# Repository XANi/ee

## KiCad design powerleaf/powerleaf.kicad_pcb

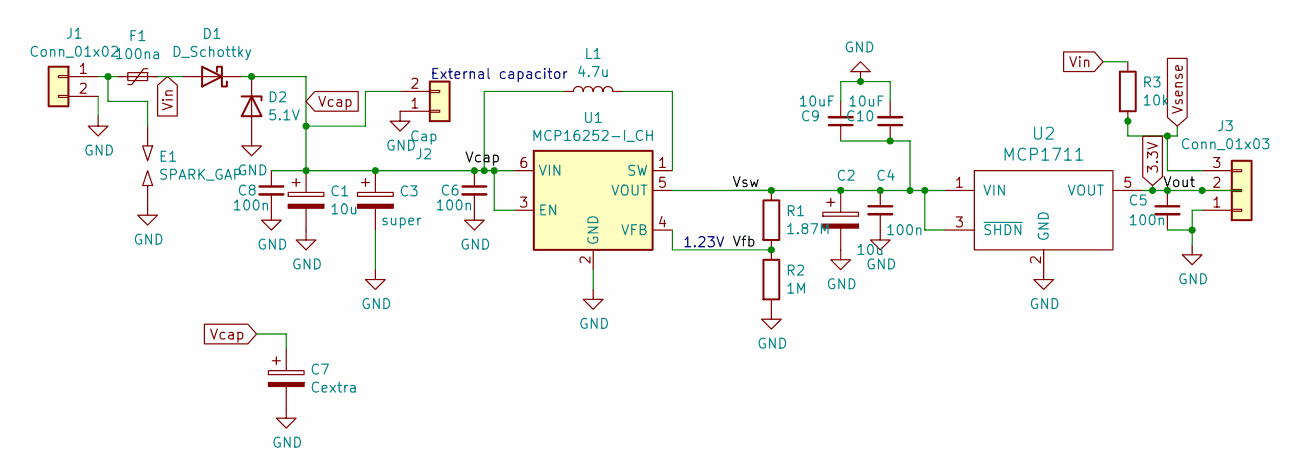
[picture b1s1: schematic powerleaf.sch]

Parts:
C1, C2: 10u; C_0805_2012Metric_Pad1.15x1.40mm_HandSolder
C3: super; CP_Radial_D10.0mm_P2.50mm_P5.00mm
C4, C5, C6: 100n; C_0805_2012Metric_Pad1.15x1.40mm_HandSolder
C7: Cextra; CP_Elec_6.3x7.7
C8: 100n; C_0805_2012Metric_Pad1.18x1.45mm_HandSolder
C9, C10: 10uF; C_0805_2012Metric_Pad1.18x1.45mm_HandSolder
D1: D_Schottky; D_0805_2012Metric_Pad1.15x1.40mm_HandSolder
D2: 5.1V; D_0805_2012Metric_Pad1.15x1.40mm_HandSolder
E1: SPARK_GAP; SparkGap-0.3mm
F1: 100na; R_Axial_DIN0204_L3.6mm_D1.6mm_P5.08mm_Vertical
J1: Conn_01x02; PinHeader_1x02_P2.54mm_Vertical
J2: Cap; PinHeader_1x02_P2.54mm_Vertical
J3: Conn_01x03; PinHeader_1x03_P2.54mm_Vertical
L1: 4.7u; L_Vishay_IHLP-1616
R1: 1.87M; R_0805_2012Metric_Pad1.15x1.40mm_HandSolder
R2: 1M; R_0805_2012Metric_Pad1.15x1.40mm_HandSolder
R3: 10k; R_0805_2012Metric_Pad1.15x1.40mm_HandSolder
U1: MCP16252-I_CH; SOT-23-6_Handsoldering
U2: MCP1711; SOT-23-6_Handsoldering

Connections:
3.3V: C5.1, J3.2, U2.5 (VOUT)
/Vfb: R1.2, R2.1, U1.4 (VFB)
/Vsw: C2.1, C4.1, C9.1, C10.1, R1.1, U1.5 (VOUT), U2.1 (VIN), U2.3 (~SHDN)
GND: C1.2, C2.2, C3.2, C4.2, C5.2, C6.2, C7.2, C8.2, C9.2, C10.2, D2.2 (A), E1.2, J1.2, J2.1, J3.1, R2.2, U1.2 (GND), U2.2 (GND)
unnamed: E1.1, F1.2, J1.1
unnamed: L1.2, U1.1 (SW)
Vcap: C1.1, C3.1, C6.1, C7.1, C8.1, D1.1 (K), D2.1 (K), J2.2, L1.1, U1.3 (EN), U1.6 (VIN)
Vin: D1.2 (A), F1.1, R3.1
Vsense: J3.3, R3.2

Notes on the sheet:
1.23V
External capacitor

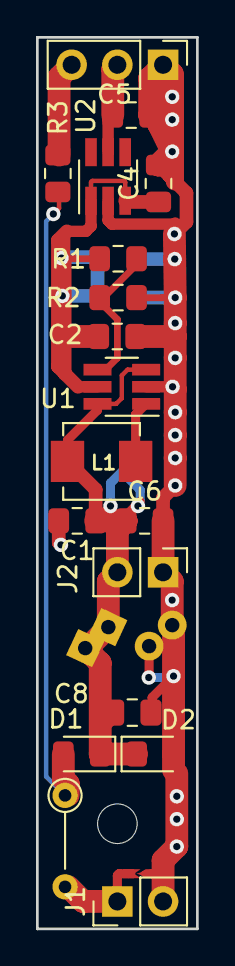
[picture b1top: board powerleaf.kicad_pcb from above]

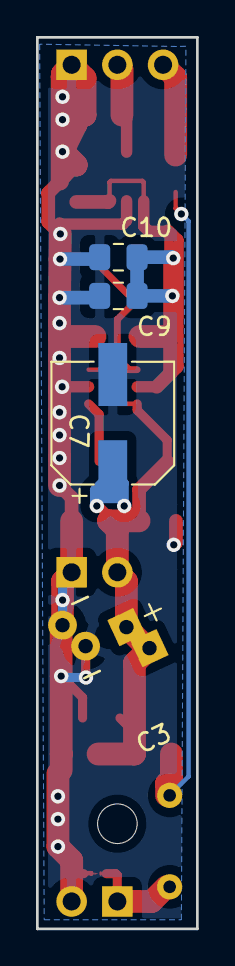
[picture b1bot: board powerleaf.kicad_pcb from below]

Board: 2 copper layers, 8.9 x 49.5 mm, 23 parts (4 on the bottom side), 9 nets.

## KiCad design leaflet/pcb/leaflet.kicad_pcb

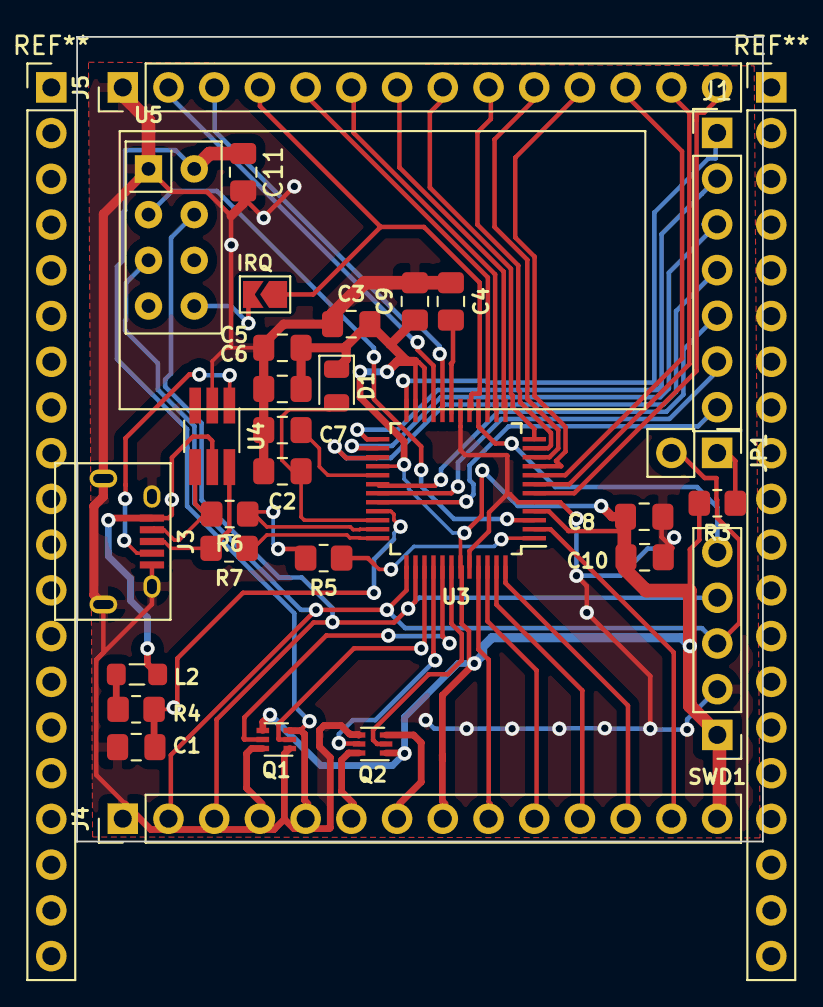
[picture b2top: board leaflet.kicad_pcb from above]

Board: 2 copper layers, 38.1 x 44.7 mm, 30 parts (0 on the bottom side), 52 nets.

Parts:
C1: 4.7u; C_0805_2012Metric_Pad1.18x1.45mm_HandSolder
C2, C7: 1u; C_0805_2012Metric_Pad1.18x1.45mm_HandSolder
C3, C4: 10n; C_0805_2012Metric_Pad1.18x1.45mm_HandSolder
C5: 10u; C_0805_2012Metric_Pad1.18x1.45mm_HandSolder
C6, C8, C9, C10, C11: 100n; C_0805_2012Metric_Pad1.18x1.45mm_HandSolder
D1: D_Schottky; D_0805_2012Metric
IRQ: Jumper_NO_Small; SolderJumper-2_P1.3mm_Open_TrianglePad1.0x1.5mm
J1: Conn_01x06_Male; PinHeader_1x07_P2.54mm_Vertical
J3: USB_B_Micro; USB_Micro-B
J4, J5: Conn_01x14_Male; PinHeader_1x14_P2.54mm_Vertical
JP1: Prog; Pin_Header_Straight_1x02_Pitch2.54mm
L2: BLM21PG221; L_0805_2012Metric_Pad1.05x1.20mm_HandSolder
Q1, Q2: NTZD3155C; SOT-563-slim
R3, R5: 3.3k; R_0805_2012Metric_Pad1.20x1.40mm_HandSolder
R4: 100; R_0805_2012Metric_Pad1.20x1.40mm_HandSolder
R6, R7: 15; R_0805_2012Metric_Pad1.20x1.40mm_HandSolder
SWD1: Conn_01x05; Pin_Header_Straight_1x05_Pitch2.54mm
U3: EFM32HG322F64G-B-QFP48; TQFP-48_7x7mm_Pitch0.5mm
U4: IP4220CZ6; TSOT-23-6_MK06A_HandSoldering
U5: NRF24L01_Breakout; nRF24L01_Breakout

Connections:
3.3V: C3.2, C4.2, C5.1, C6.1, C8.1, C9.1, C10.1, D1.1, J4.8, J4.14, Q1.4, Q2.1, R3.2, SWD1.1, U3.4, U3.19, U3.22, U3.23, U3.28, U3.43
/Prog/I2C_PULLUP: JP1.1, R3.1
/USB/D+: R7.1, U3.36
/USB/D-: R5.2, R6.1, U3.35
/USB/DR+: J3.3, R7.2, U4.6
/USB/DR-: J3.2, R6.2, U4.4
/USB/ID: J3.4, U4.1
/USB/USB_5V: L2.2, R4.1
/USB/VBUS: J3.1, L2.1, U4.5
AUX1_3.3V: C11.1, J4.5, Q1.3, U5.2
AUX2_3.3V: J4.6, Q2.6
GND: C1.2, C2.2, C3.1, C4.1, C5.2, C6.2, C7.2, C8.2, C9.2, C10.2, C11.2, J3.5, J3.6, J4.1, J5.1, Q1.1, Q2.4, SWD1.2, U3.5, U3.18, U3.44, U4.2, U5.1
I2C_SCL: J5.13, U3.7
I2C_SDA: J5.14, U3.6
unnamed: C7.1, U3.29
unnamed: IRQ.2, U5.8
unnamed: Q1.2, U3.39
unnamed: Q1.5, U3.41
unnamed: Q2.2, U3.42
unnamed: Q2.5, U3.40
OUT_OD1: J4.4, Q1.6
OUT_OD2: J4.7, Q2.3
PA1: J4.13, U3.2
PA8: J5.7, U3.13
PA9: J5.6, U3.14
PA10: J5.5, U3.15
PB11: IRQ.1, J5.4, U3.17
PC2: J5.12, U3.8
PC3: J5.11, U3.9
PC4: J5.10, U3.10
PC8: J1.5, U3.30
PC9: J1.6, U3.31
PC10: J1.7, U3.32
PD4: J1.1, U3.24
PD5: J1.2, U3.25
PE10: J4.9, U3.45
PE11: J4.10, U3.46
PE12: J4.11, U3.47
PE13: J4.12, U3.48
RESET: SWD1.5, U3.16
USART0_CLK: J5.3, U3.20
USART0_CS: J5.2, U3.21
USART0_RX_MISO: J5.8, U3.12
USART0_TX_MOSI: J5.9, U3.11
USART1_CE: U3.3, U5.3
USART1_CS: J4.3, SWD1.4, U3.38, U5.4
USART1_RX_MISO: J1.3, U3.26
USART1_SCK: J4.2, JP1.2, SWD1.3, U3.37, U5.5
USART1_TX_MOSI: J1.4, U3.27
USB_5v: C1.1, R4.2, U3.33
USB_DMPU: R5.1, U3.1
USB_VREGO: C2.1, D1.2, U3.34

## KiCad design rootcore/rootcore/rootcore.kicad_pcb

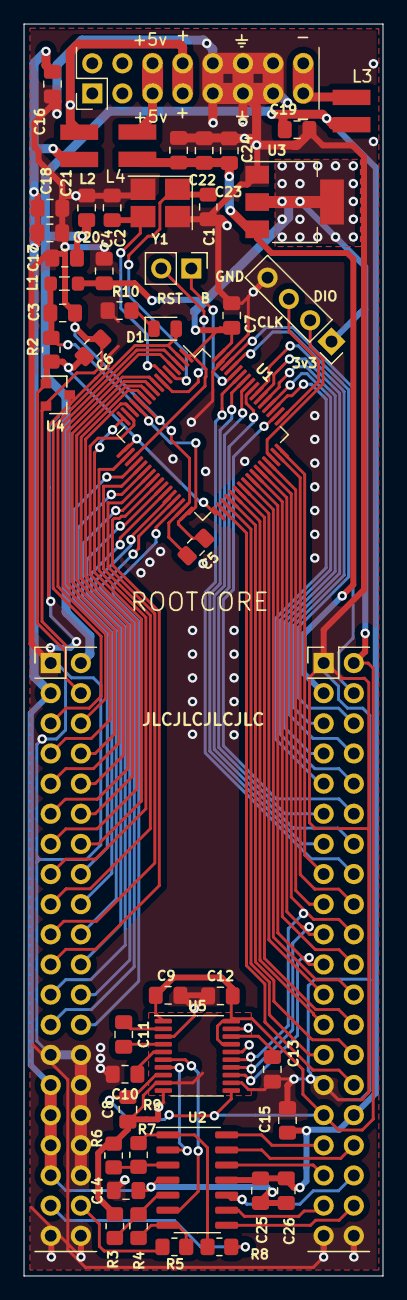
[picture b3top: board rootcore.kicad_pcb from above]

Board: 2 copper layers, 30.2 x 105.5 mm, 52 parts (0 on the bottom side), 85 nets.

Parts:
C1, C2: 18p; C_0805_2012Metric_Pad1.18x1.45mm_HandSolder
C3, C4, C5, C6, C8, C9, C12, C13, C14, C15, C22, C25: 100n; C_0805_2012Metric_Pad1.18x1.45mm_HandSolder
C7, C16, C17, C18, C19, C20, C21, C23, C24, C26: 22u; C_0805_2012Metric_Pad1.18x1.45mm_HandSolder
C10, C11: 2.2u; C_0805_2012Metric_Pad1.18x1.45mm_HandSolder
D1: LED; LED_0805_2012Metric
J1, J2: Conn_02x20_Odd_Even; PinHeader_2x20_P2.54mm_Vertical
J3: Conn_02x08_Odd_Even; PinHeader_2x08_P2.54mm_Vertical
J4: Conn_01x04_Male; PinSocket_1x04_P2.54mm_Vertical
J5: Conn_01x02_Male; PinHeader_1x02_P2.54mm_Vertical
L1: 100u; L_0805_2012Metric_Pad1.05x1.20mm_HandSolder
L2, L3, L4: 100u >300mA; YP0302
R1, R9: 0; NetTie-2_SMD_Pad0.5mm
R2, R5, R8: 1k; R_0805_2012Metric_Pad1.20x1.40mm_HandSolder
R3, R6: 20k; R_0805_2012Metric_Pad1.20x1.40mm_HandSolder
R4, R7: 13k; R_0805_2012Metric_Pad1.20x1.40mm_HandSolder
R10: 220; R_0805_2012Metric_Pad1.20x1.40mm_HandSolder
U1: STM32F373RCTx; LQFP-64_10x10mm_P0.5mm
U2: TL074; SOIC-14_3.9x8.7mm_P1.27mm
U3: AP1117-15; SOT-223-3_TabPin2
U4: LM4040DBZ-2.5; SOT-23
U5: PCM5100; TSSOP-20_4.4x6.5mm_P0.65mm
Y1: Crystal_GND24; Crystal_SMD_TXC_7M-4Pin_3.2x2.5mm_HandSoldering

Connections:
3v3: C4.1, C7.1, C8.2, C9.2, C12.2, J1.2, J1.31, J4.1, L1.1, U1.1, U1.19, U1.64, U3.2, U5.1, U5.8, U5.11, U5.17, U5.20
3v3a: C3.1, C5.1, L1.2, R2.1, U1.13, U1.32
5v: C22.1, C23.1, C24.1, J1.3, L4.2, U3.3
5vRAW: J3.5, J3.6, L4.1
12v: C14.1, C16.1, C18.1, C20.1, C25.1, C26.1, J2.3, J2.29, J2.31, J2.33, J2.35, L2.2, U2.4
12vRAW: J3.7, J3.8, L2.1
-12v: C15.2, C17.2, C19.2, C21.2, C25.2, C26.2, J1.32, J2.2, L3.2, U2.11
-12vRAW: J3.15, J3.16, L3.1
BOOT0: J5.1, U1.60
DAC_BCK: J1.21, U1.41, U5.13
DAC_DIN: J1.19, U1.43, U5.14
DAC_L: U2.6, U5.6
DAC_LRCK: J1.20, U1.44, U5.15
DAC_R: U2.2, U5.7
GND: C1.2, C2.2, C4.2, C7.2, C9.1, C10.2, C12.1, C13.2, C14.2, C15.1, C16.2, C17.1, C18.2, C19.1, C20.2, C21.1, C22.2, C23.2, C24.2, J1.1, J1.29, J1.39, J1.40, J2.1, J2.27, J2.28, J2.30, J2.32, J2.34, J2.36, J2.39, J2.40, J3.9, J3.10, J3.11, J3.12, J3.13, J3.14, J4.4, R1.1, R9.2, R10.2, U1.63, U3.1, U5.3, U5.10, U5.12, U5.16, U5.19, Y1.2, Y1.4
GNDA: C3.2, C5.2, C6.2, R1.2, U1.12, U1.31, U4.2
GNDS: C8.1, R3.2, R6.2, R9.1, U5.9
NRST: J5.2, U1.7
unnamed: C10.1, U5.5
unnamed: C11.1, U5.2
unnamed: C11.2, U5.4
unnamed: C13.1, U5.18
unnamed: D1.1, R10.1
unnamed: R3.1, R4.1, U2.5
unnamed: R4.2, R5.1, U2.7
unnamed: R6.1, R7.1, U2.3
unnamed: R7.2, R8.1, U2.1
OP1_INN: J1.34, U2.13
OP1_INP: J1.35, U2.12
OP1_OUT: J1.33, U2.14
OP2_INN: J1.37, U2.9
OP2_INP: J1.36, U2.10
OP2_OUT: J1.38, U2.8
OUT_L: J2.38, R5.2
OUT_R: J2.37, R8.2
PA0: J2.12, U1.14
PA1: J2.13, U1.15
PA2: J2.14, U1.16
PA3: J2.15, U1.18
PA4: J2.16, U1.20
PA5: J2.17, U1.21
PA6: J2.18, U1.22
PA7: J2.19, U1.23
PA9: J1.22, U1.42
PA12: J1.17, U1.45
PA13: J4.2, U1.46
PA14: J4.3, U1.49
PA15: J1.12, U1.50
PB0: J2.22, U1.26
PB1: J2.23, U1.27
PB2: J2.24, U1.28
PB3: J1.5, U1.55
PB4: J1.11, U1.56
PB5: J1.14, U1.57
PB6: J1.13, U1.58
PB7: J1.16, U1.59
PB8: J1.6, U1.61
PB9: J1.4, U1.62
PB14: J1.30, U1.34
PB15: J1.27, U1.35
PC0: J2.8, U1.8
PC1: J2.9, U1.9
PC2: J2.10, U1.10
PC3: J2.11, U1.11
PC4: J2.20, U1.24
PC5: J2.21, U1.25
PC6: J1.25, U1.37
PC7: J1.26, U1.38
PC8: J1.23, U1.39
PC9: J1.24, U1.40
PC10: J1.9, U1.51
PC11: J1.10, U1.52
PC12: J1.7, U1.53
PC13: D1.2, J2.5, U1.2
PC14: J2.6, U1.3
PC15: J2.7, U1.4
PD2: J1.8, U1.54
PD8: J1.28, U1.36
PE8: J2.25, U1.29
PE9: J2.26, U1.30
PF0: C1.1, U1.5, Y1.1
PF1: C2.1, U1.6, Y1.3
PF6: J1.18, U1.47
PF7: J1.15, U1.48
Ref2v5: C6.1, J2.4, R2.2, U1.17, U1.33, U4.1

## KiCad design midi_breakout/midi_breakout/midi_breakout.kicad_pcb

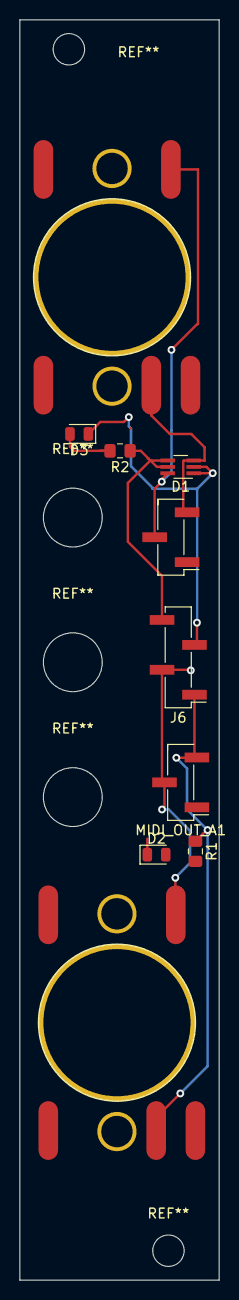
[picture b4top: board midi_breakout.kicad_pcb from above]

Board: 2 copper layers, 20.3 x 128.5 mm, 10 parts (0 on the bottom side), 8 nets.

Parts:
D1: BAS70BRW; SOT-363_SC-70-6_Handsoldering
D2, D3: LED; LED_0805_2012Metric
IN: DIN-5_180degree; DIN-5-ext
IN AB: Conn_01x03; PinHeader_1x03_P2.54mm_Vertical_SMD_Pin1Left
J6: Conn_01x04; PinHeader_1x04_P2.54mm_Vertical_SMD_Pin1Left
MIDI_OUT_A1: Conn_01x03; PinHeader_1x03_P2.54mm_Vertical_SMD_Pin1Left
OUT: DIN-5_180degree; DIN-5-ext
R1, R2: R; R_0805_2012Metric_Pad1.15x1.40mm_HandSolder

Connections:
Midi_in_+: D1.4, D1.5, J6.4, R2.1
Midi_in_-: D1.1, D1.2, D3.1, J6.3
Midi_out_+: D2.1, J6.1, MIDI_OUT_A1.3, OUT.4, R1.1
Midi_out_-: J6.2, MIDI_OUT_A1.2, OUT.5
unnamed: D1.3, IN.4, IN AB.3
unnamed: D1.6, IN.5, IN AB.2
unnamed: D2.2, R1.2
unnamed: D3.2, R2.2

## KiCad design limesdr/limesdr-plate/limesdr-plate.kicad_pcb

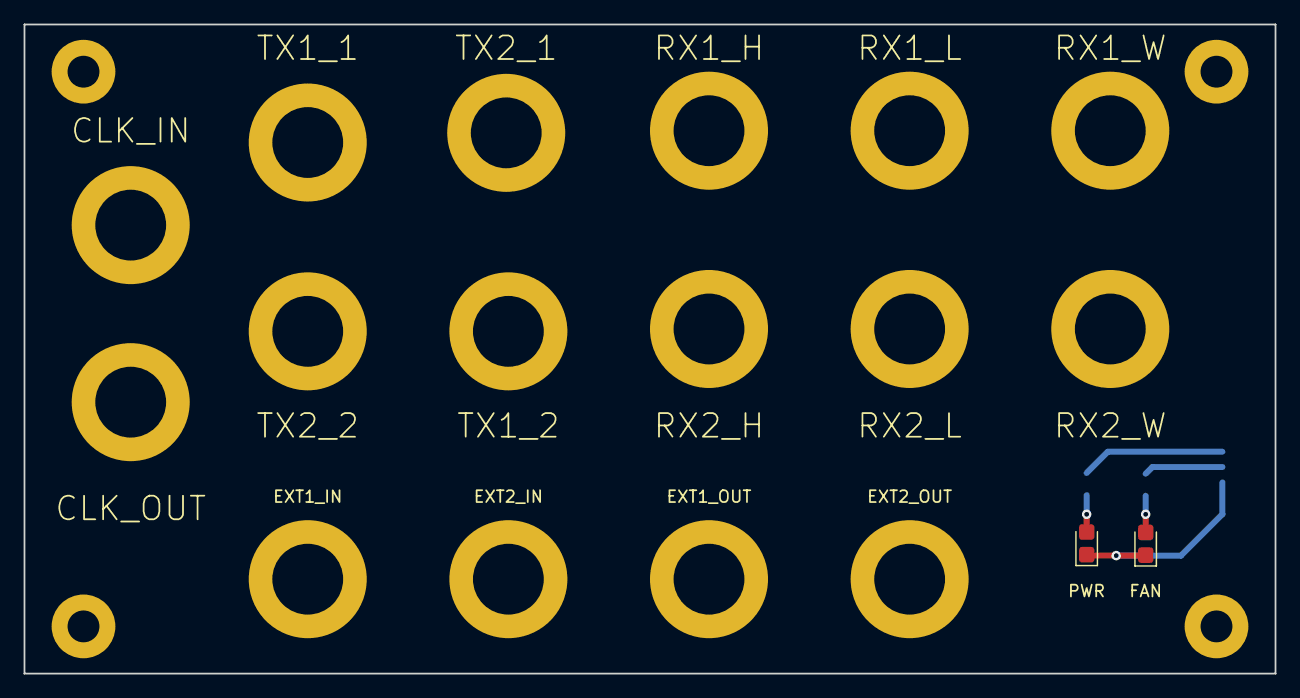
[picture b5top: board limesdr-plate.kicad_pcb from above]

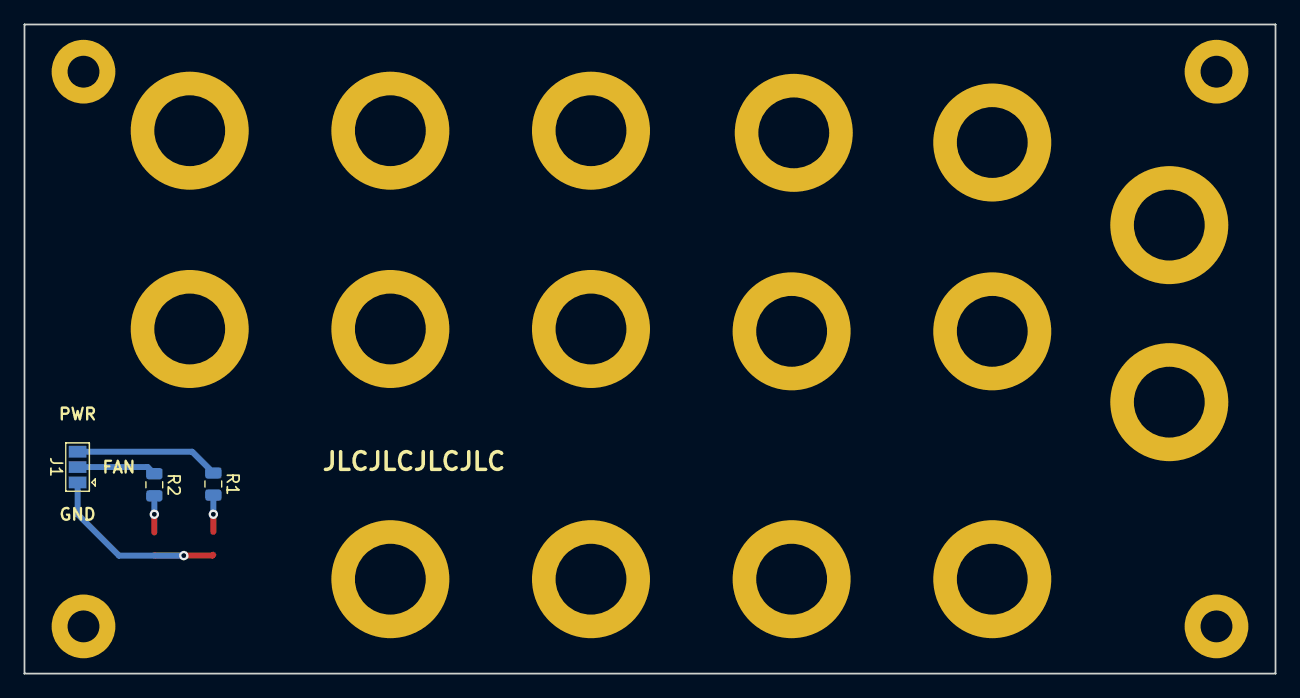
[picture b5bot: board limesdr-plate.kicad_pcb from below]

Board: 2 copper layers, 106.0 x 55.0 mm, 21 parts (3 on the bottom side), 4 nets.

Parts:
CLK_IN: MountingHole_6mm_Pad
CLK_OUT: MountingHole_6mm_Pad
EXT1_IN, EXT1_OUT, EXT2_IN, EXT2_OUT: MountingHole_6mm_Pad
FAN: LED; D_0805_2012Metric_Castellated
J1: Conn_01x03_Male; SolderJumper-3_P1.3mm_Open_Pad1.0x1.5mm
PWR: LED; D_0805_2012Metric_Castellated
R1, R2: R; R_0805_2012Metric
RX1_H, RX1_L, RX1_W, RX2_H, RX2_L, RX2_W: MountingHole_6mm_Pad
TX1_1, TX1_2, TX2_1, TX2_2: MountingHole_6mm_Pad

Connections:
GND: FAN.1, J1.1, PWR.1
unnamed: PWR.2, R1.2
unnamed: FAN.2, R2.2
unnamed: J1.2, R2.1

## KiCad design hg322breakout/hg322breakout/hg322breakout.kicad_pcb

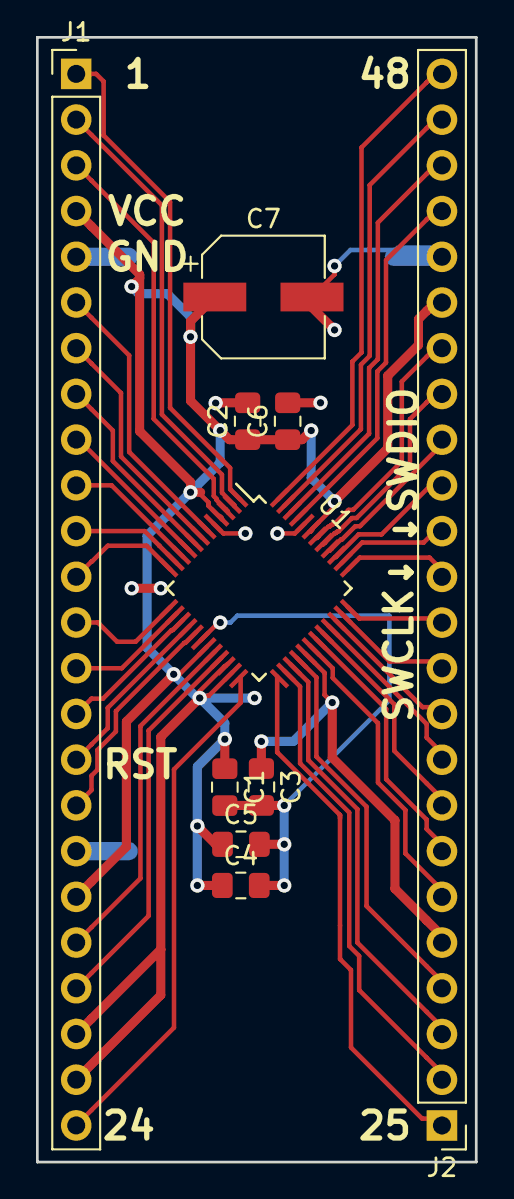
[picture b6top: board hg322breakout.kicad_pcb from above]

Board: 2 copper layers, 24.4 x 62.5 mm, 10 parts (0 on the bottom side), 42 nets.

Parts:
C1, C2, C4, C5, C6: 100n; C_0805_2012Metric_Pad1.15x1.40mm_HandSolder
C3: 1u; C_0805_2012Metric_Pad1.15x1.40mm_HandSolder
C7: 47u; CP_Elec_6.3x3.9
J1, J2: Conn_01x24_Male; PinHeader_1x24_P2.54mm_Vertical
U1: EFM32HG322F64G-B-QFP48; TQFP-48_7x7mm_P0.5mm

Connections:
PIN1: J1.1, U1.1
PIN2: J1.2, U1.2
PIN3: J1.3, U1.3
PIN6: J1.6, U1.6
PIN7: J1.7, U1.7
PIN8: J1.8, U1.8
PIN9: J1.9, U1.9
PIN10: J1.10, U1.10
PIN11: J1.11, U1.11
PIN12: J1.12, U1.12
PIN13: J1.13, U1.13
PIN14: J1.14, U1.14
PIN15: J1.15, U1.15
PIN16: J1.16, U1.16
PIN17: J1.17, U1.17
PIN18: C1.2, C2.2, C3.2, C4.2, C5.2, C6.2, C7.2, J1.5, J1.18, J2.20, U1.5, U1.18, U1.44
PIN19: C1.1, C2.1, C4.1, C5.1, C6.1, C7.1, J1.4, J1.19, J1.22, J1.23, J2.19, U1.4, U1.19, U1.22, U1.23, U1.43
PIN20: J1.20, U1.20
PIN21: J1.21, U1.21
PIN24: J1.24, U1.24
PIN25: J2.1, U1.25
PIN26: J2.2, U1.26
PIN27: J2.3, U1.27
PIN28: J2.4, U1.28
PIN29: C3.1, J2.5, U1.29
PIN30: J2.6, U1.30
PIN31: J2.7, U1.31
PIN32: J2.8, U1.32
PIN33: J2.9, U1.33
PIN34: J2.10, U1.34
PIN35: J2.11, U1.35
PIN36: J2.12, U1.36
PIN37: J2.13, U1.37
PIN38: J2.14, U1.38
PIN39: J2.15, U1.39
PIN40: J2.16, U1.40
PIN41: J2.17, U1.41
PIN42: J2.18, U1.42
PIN45: J2.21, U1.45
PIN46: J2.22, U1.46
PIN47: J2.23, U1.47
PIN48: J2.24, U1.48

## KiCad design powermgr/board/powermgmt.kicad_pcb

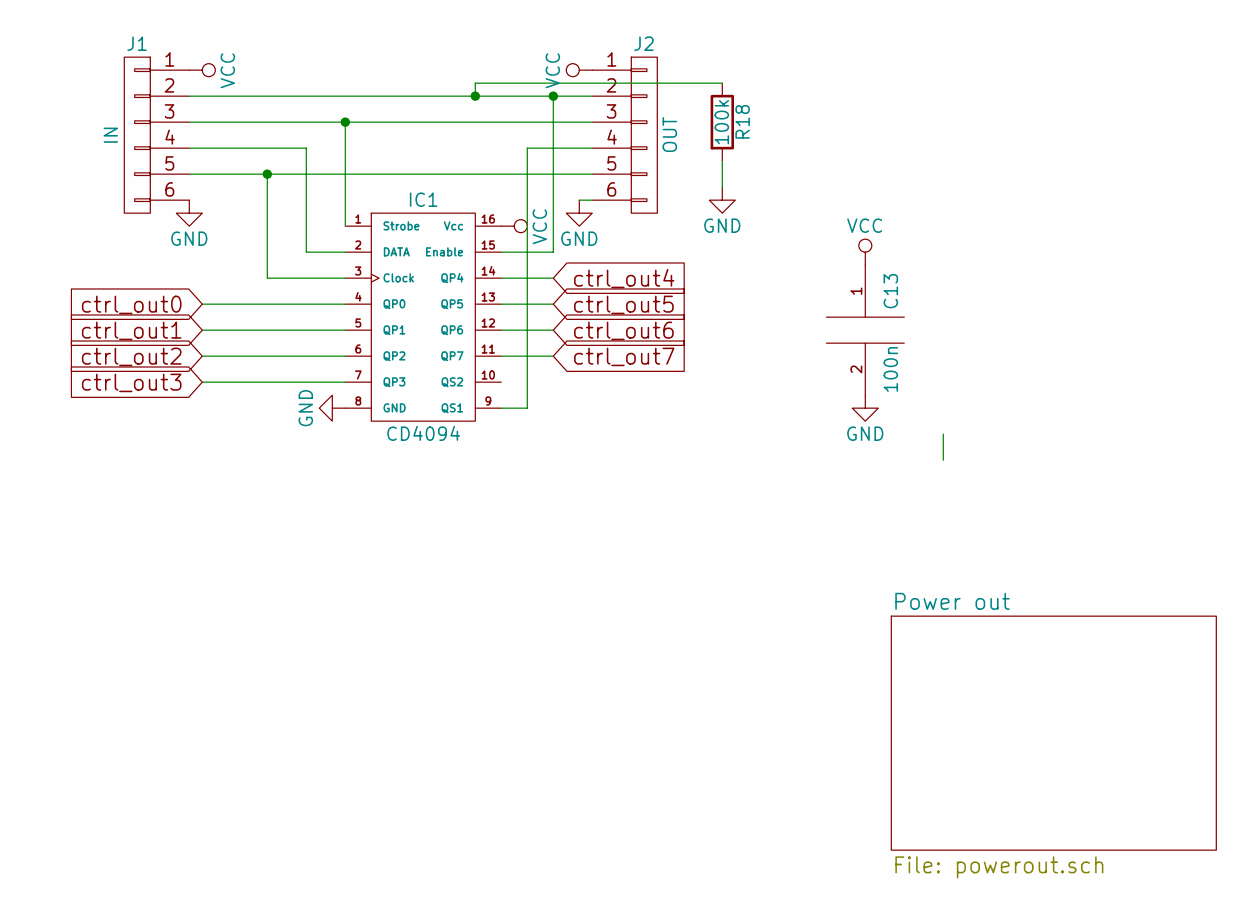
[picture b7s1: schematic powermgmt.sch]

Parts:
C13: 100n; C_0805_HandSoldering
IC1: CD4094; TSSOP-16_4.4x5mm_Pitch0.65mm
J1: IN; Pin_Header_Straight_1x06_Pitch2.54mm
J2: OUT; Pin_Header_Straight_1x06_Pitch2.54mm
R18: 100k; R_0805_HandSoldering

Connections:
GND: C13.2, IC1.8 (GND), J1.6, J2.6, R18.2; also elsewhere on the board
unnamed: IC1.1 (Strobe), J1.3, J2.3
unnamed: IC1.2 (DATA), J1.4
unnamed: IC1.3 (Clock), J1.5, J2.5
unnamed: IC1.9 (QS1), J2.4
unnamed: IC1.15 (Enable), J1.2, J2.2, R18.1
VCC: C13.1, IC1.16 (Vcc), J1.1, J2.1
ctrl_out0: IC1.4 (QP0); also elsewhere on the board
ctrl_out1: IC1.5 (QP1); also elsewhere on the board
ctrl_out2: IC1.6 (QP2); also elsewhere on the board
ctrl_out3: IC1.7 (QP3); also elsewhere on the board
ctrl_out4: IC1.14 (QP4); also elsewhere on the board
ctrl_out5: IC1.13 (QP5); also elsewhere on the board
ctrl_out6: IC1.12 (QP6); also elsewhere on the board
ctrl_out7: IC1.11 (QP7); also elsewhere on the board

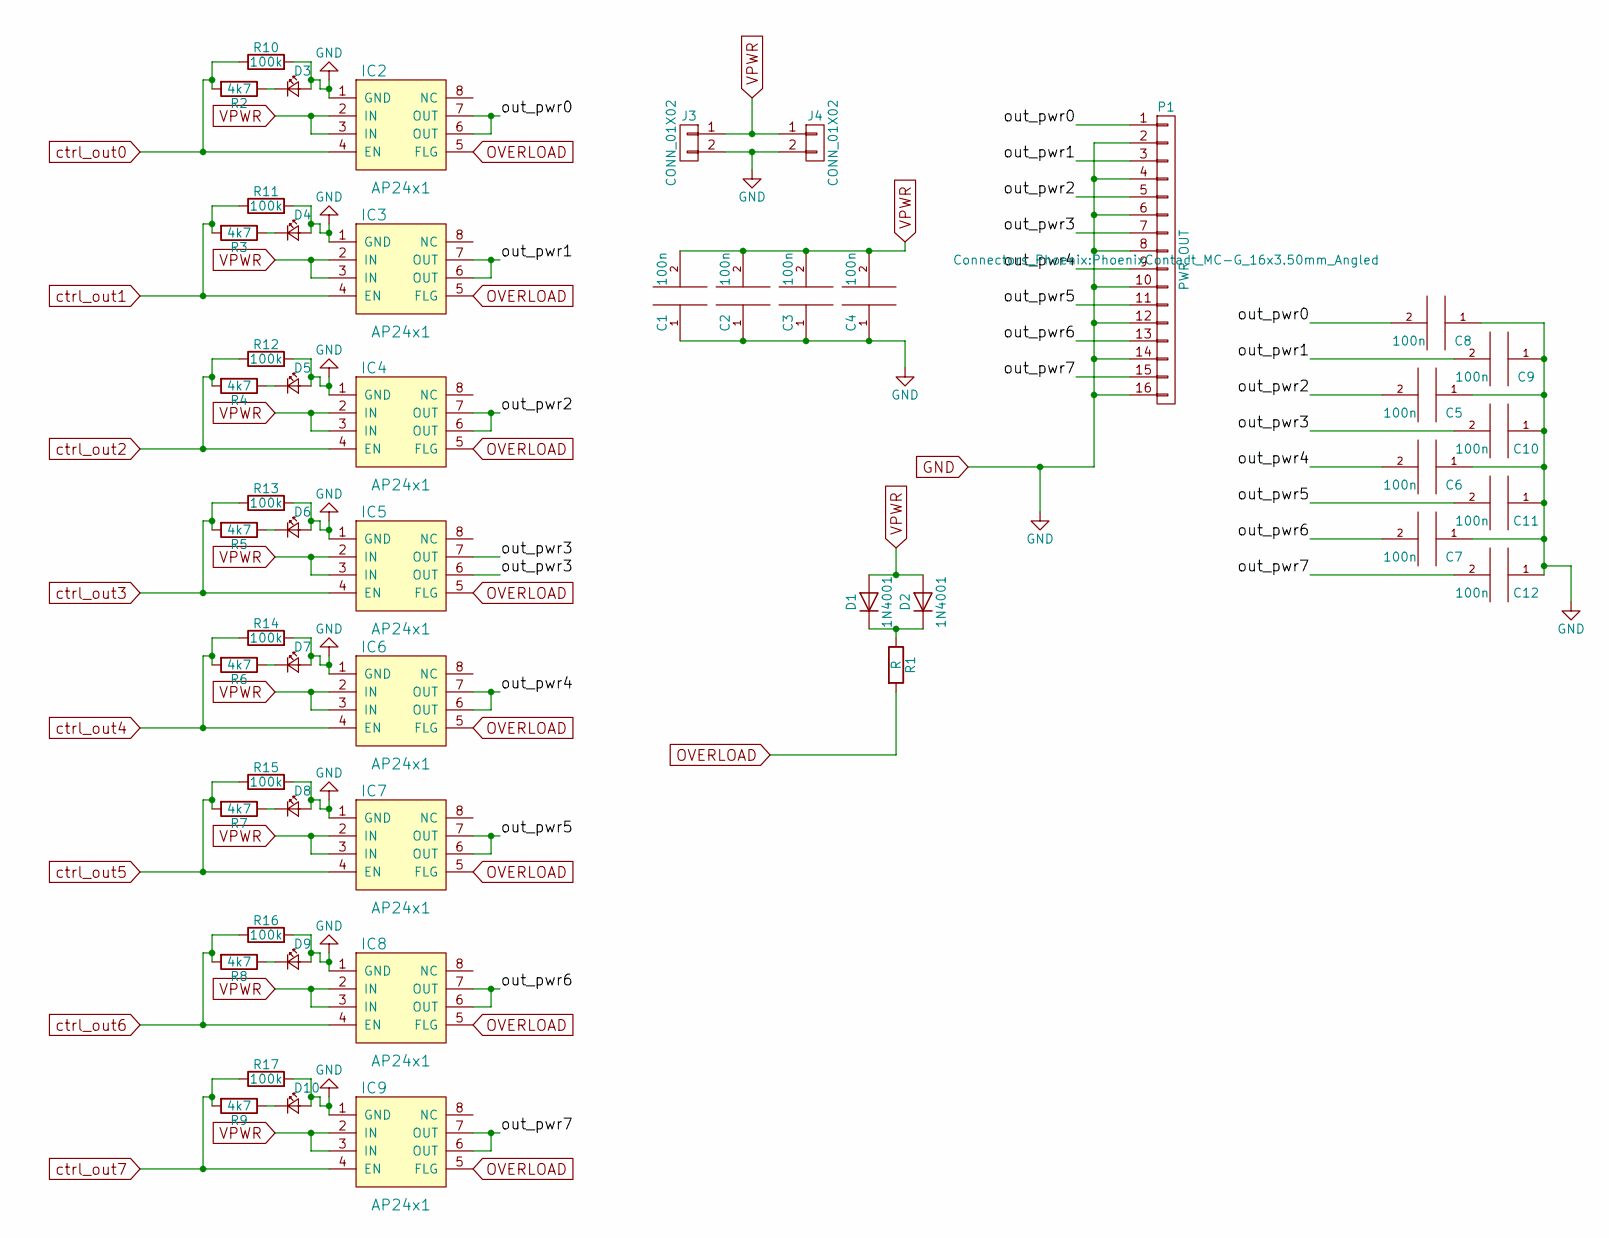
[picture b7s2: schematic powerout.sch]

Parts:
C1, C2, C3, C4, C5, C6, C7, C8, C9, C10, C11, C12: 100n; C_0805_HandSoldering
D1: 1N4001; LED_0805
D2: 1N4001; LED_D5.0mm
D3, D4, D5, D6, D7, D8, D9, D10: LED_Small; LED_0805
IC2, IC3, IC4, IC5, IC6, IC7, IC8, IC9: AP24x1; SOIC-8_3.9x4.9mm_Pitch1.27mm
J3, J4: CONN_01X02; PhoenixContact_GMSTBVA-G_02x7.62mm_Vertical
P1: PWR_OUT; PhoenixContact_MC-G_16x3.50mm_Angled
R1: R; R_0805_HandSoldering
R2, R3, R4, R5, R6, R7, R8, R9: 4k7; R_0805_HandSoldering
R10, R11, R12, R13, R14, R15, R16, R17: 100k; R_0805_HandSoldering

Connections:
/Power out/out_pwr0: C8.2, IC2.6 (OUT), IC2.7 (OUT), P1.1
/Power out/out_pwr1: C9.2, IC3.6 (OUT), IC3.7 (OUT), P1.3
/Power out/out_pwr2: C5.2, IC4.6 (OUT), IC4.7 (OUT), P1.5
/Power out/out_pwr3: C10.2, IC5.6 (OUT), IC5.7 (OUT), P1.7
/Power out/out_pwr4: C6.2, IC6.6 (OUT), IC6.7 (OUT), P1.9
/Power out/out_pwr5: C11.2, IC7.6 (OUT), IC7.7 (OUT), P1.11
/Power out/out_pwr6: C7.2, IC8.6 (OUT), IC8.7 (OUT), P1.13
/Power out/out_pwr7: C12.2, IC9.6 (OUT), IC9.7 (OUT), P1.15
GND: C1.1, C2.1, C3.1, C4.1, C5.1, C6.1, C7.1, C8.1, C9.1, C10.1, C11.1, C12.1, D3.2 (A), D4.2 (A), D5.2 (A), D6.2 (A), D7.2 (A), D8.2 (A), D9.2 (A), D10.2 (A), IC2.1 (GND), IC3.1 (GND), IC4.1 (GND), IC5.1 (GND), IC6.1 (GND), IC7.1 (GND), IC8.1 (GND), IC9.1 (GND), J3.2, J4.2, P1.2, P1.4, P1.6, P1.8, P1.10, P1.12, P1.14, P1.16, R10.2, R11.2, R12.2, R13.2, R14.2, R15.2, R16.2, R17.2; also elsewhere on the board
unnamed: D1.1 (K), D2.1 (K), R1.1
unnamed: D3.1 (K), R2.1
unnamed: D4.1 (K), R3.1
unnamed: D5.1 (K), R4.1
unnamed: D6.1 (K), R5.1
unnamed: D7.1 (K), R6.1
unnamed: D8.1 (K), R7.1
unnamed: D9.1 (K), R8.1
unnamed: D10.1 (K), R9.1
OVERLOAD: IC2.5 (FLG), IC3.5 (FLG), IC4.5 (FLG), IC5.5 (FLG), IC6.5 (FLG), IC7.5 (FLG), IC8.5 (FLG), IC9.5 (FLG), R1.2
VPWR: C1.2, C2.2, C3.2, C4.2, D1.2 (A), D2.2 (A), IC2.2 (IN), IC2.3 (IN), IC3.2 (IN), IC3.3 (IN), IC4.2 (IN), IC4.3 (IN), IC5.2 (IN), IC5.3 (IN), IC6.2 (IN), IC6.3 (IN), IC7.2 (IN), IC7.3 (IN), IC8.2 (IN), IC8.3 (IN), IC9.2 (IN), IC9.3 (IN), J3.1, J4.1
ctrl_out0: IC2.4 (EN), R2.2, R10.1; also elsewhere on the board
ctrl_out1: IC3.4 (EN), R3.2, R11.1; also elsewhere on the board
ctrl_out2: IC4.4 (EN), R4.2, R12.1; also elsewhere on the board
ctrl_out3: IC5.4 (EN), R5.2, R13.1; also elsewhere on the board
ctrl_out4: IC6.4 (EN), R6.2, R14.1; also elsewhere on the board
ctrl_out5: IC7.4 (EN), R7.2, R15.1; also elsewhere on the board
ctrl_out6: IC8.4 (EN), R8.2, R16.1; also elsewhere on the board
ctrl_out7: IC9.4 (EN), R9.2, R17.1; also elsewhere on the board

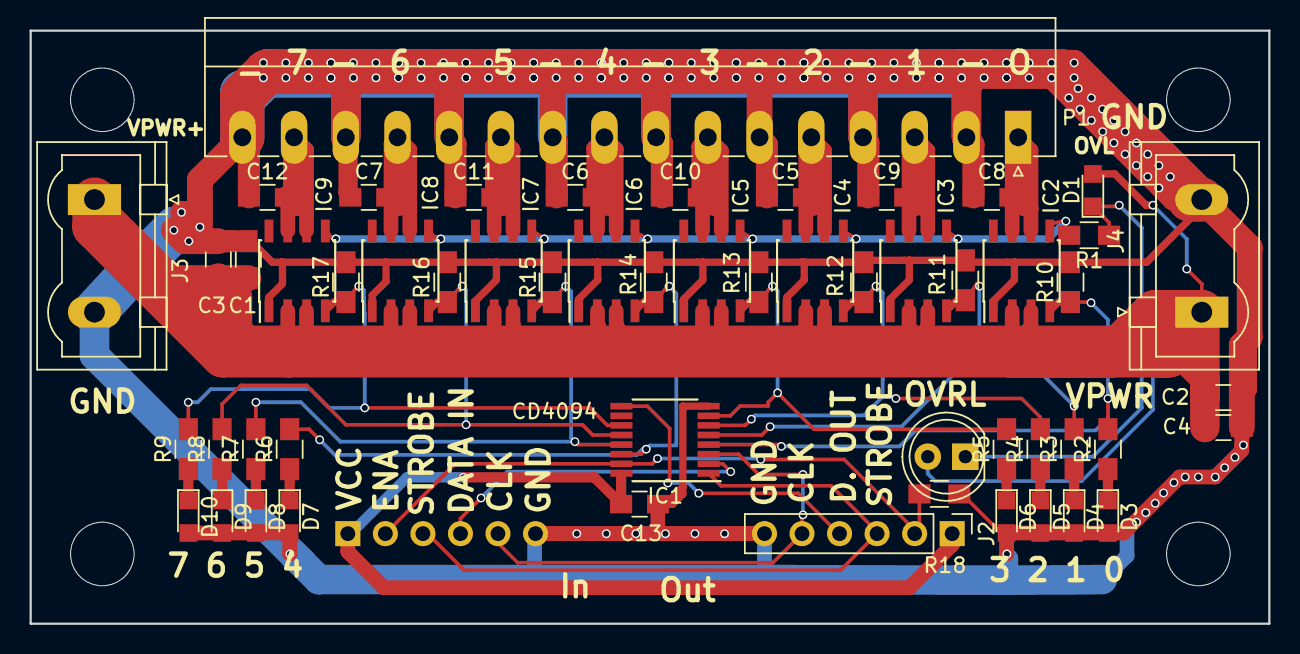
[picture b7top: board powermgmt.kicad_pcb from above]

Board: 2 copper layers, 83.8 x 40.1 mm, 55 parts (1 on the bottom side), 34 nets.

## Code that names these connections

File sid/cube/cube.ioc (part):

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PB13.GPIOParameters=GPIO_PuPd,GPIO_Label
Mcu.UserName=STM32F103C8Tx
PB10.GPIO_PuPd=GPIO_NOPULL
PC13-TAMPER-RTC.GPIOParameters=GPIO_Label
PB14.GPIO_Label=SID_D6
PA3.GPIOParameters=GPIO_Label
PA6.GPIO_Label=SID_RW
PB0.GPIO_Label=SID_RST
PB11.GPIO_PuPd=GPIO_NOPULL
PB13.GPIO_Label=SID_D5
PB11.Signal=GPIO_Output
PB13.Signal=GPIO_Output
PB15.Signal=GPIO_Output
PA2.GPIOParameters=GPIO_Label
RCC.SYSCLKSource=RCC_SYSCLKSOURCE_PLLCLK
PD1-OSC_OUT.Signal=RCC_OSC_OUT
PA0-WKUP.GPIOParameters=GPIO_Label
PB12.GPIO_Label=SID_D4
PB0.GPIOParameters=GPIO_Label
PA1.GPIOParameters=GPIO_Label
PC14-OSC32_IN.Mode=LSE-External-Oscillator
PA14.Mode=Serial_Wire
PA8.Signal=RCC_MCO
Mcu.Package=LQFP48
PB9.Signal=GPIO_Output
PB14.GPIO_PuPd=GPIO_NOPULL
PA6.Signal=GPIO_Output
PB15.GPIO_PuPd=GPIO_NOPULL
PA2.GPIO_Label=SID_A2
PA10.Signal=USART1_RX
PA5.GPIOParameters=GPIO_Label
PB14.GPIOParameters=GPIO_PuPd,GPIO_Label
PB10.GPIOParameters=GPIO_PuPd,GPIO_Label
PA4.GPIO_Label=SID_A0
PA3.Signal=GPIO_Output
PA6.GPIOParameters=GPIO_Label
PC15-OSC32_OUT.Mode=LSE-External-Oscillator
PB8.GPIOParameters=GPIO_Label
PD1-OSC_OUT.Mode=HSE-External-Oscillator
PB9.GPIO_Label=SID_D1
PA10.Mode=Asynchronous
PB11.GPIO_Label=SID_D3
PC13-TAMPER-RTC.Signal=GPIO_Output
PD0-OSC_IN.Signal=RCC_OSC_IN
PC14-OSC32_IN.Signal=RCC_OSC32_IN
PA0-WKUP.GPIO_Label=SID_A4
PA0-WKUP.Signal=GPIO_Output
PB9.GPIOParameters=GPIO_Label
PA13.Signal=SYS_JTMS-SWDIO
PB8.GPIO_Label=SID_D0
PA9.Mode=Asynchronous
PB10.GPIO_Label=SID_D2
PA9.Signal=USART1_TX
PB11.GPIOParameters=GPIO_PuPd,GPIO_Label
PC15-OSC32_OUT.Signal=RCC_OSC32_OUT
PA1.Signal=GPIO_Output
PD0-OSC_IN.Mode=HSE-External-Oscillator
PB10.Signal=GPIO_Output
PB14.Signal=GPIO_Output
PA5.Signal=GPIO_Output
board=custom
PC13-TAMPER-RTC.GPIO_Label=LED
PB13.GPIO_PuPd=GPIO_NOPULL
PB15.GPIO_Label=SID_D7
PA1.GPIO_Label=SID_A3
PA4.GPIOParameters=GPIO_Label
PB15.GPIOParameters=GPIO_PuPd,GPIO_Label
PA13.Mode=Serial_Wire
Mcu.Name=STM32F103C(8-B)Tx
PA2.Signal=GPIO_Output
PA4.Signal=GPIO_Output
RCC.SYSCLKFreq_VALUE=72000000
PA7.GPIO_Label=SID_CLK
PA5.GPIO_Label=SID_CS
PA14.Signal=SYS_JTCK-SWCLK
PB8.Signal=GPIO_Output
PA8.Mode=Clock-out
PB12.GPIO_PuPd=GPIO_NOPULL
PB0.Signal=GPIO_Output
PA7.GPIOParameters=GPIO_Label
PB12.GPIOParameters=GPIO_PuPd,GPIO_Label
PB12.Signal=GPIO_Output
PA3.GPIO_Label=SID_A1
PA7.Signal=S_TIM3_CH2

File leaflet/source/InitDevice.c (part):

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
	// $[Port B Configuration]

	/* Pin PB7 is configured to Push-pull */
	GPIO->P[1].MODEL = (GPIO->P[1].MODEL & ~_GPIO_P_MODEL_MODE7_MASK)
			| GPIO_P_MODEL_MODE7_PUSHPULL;

	/* Pin PB8 is configured to Input enabled */
	GPIO->P[1].MODEH = (GPIO->P[1].MODEH & ~_GPIO_P_MODEH_MODE8_MASK)
			| GPIO_P_MODEH_MODE8_INPUT;

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	GPIO->P[1].MODEH = (GPIO->P[1].MODEH & ~_GPIO_P_MODEH_MODE13_MASK)
			| GPIO_P_MODEH_MODE13_PUSHPULL;

	/* Pin PB14 is configured to Push-pull */
	GPIO->P[1].MODEH = (GPIO->P[1].MODEH & ~_GPIO_P_MODEH_MODE14_MASK)
			| GPIO_P_MODEH_MODE14_PUSHPULL;
	// [Port B Configuration]$

	// $[Port C Configuration]

	/* Pin PC0 is configured to Open-drain with pull-up and filter */
	GPIO->P[2].MODEL = (GPIO->P[2].MODEL & ~_GPIO_P_MODEL_MODE0_MASK)
			| GPIO_P_MODEL_MODE0_WIREDANDPULLUPFILTER;

	/* Pin PC1 is configured to Open-drain with pull-up and filter */
	GPIO->P[2].MODEL = (GPIO->P[2].MODEL & ~_GPIO_P_MODEL_MODE1_MASK)
			| GPIO_P_MODEL_MODE1_WIREDANDPULLUPFILTER;

	/* Pin PC2 is configured to Input enabled */
	GPIO->P[2].MODEL = (GPIO->P[2].MODEL & ~_GPIO_P_MODEL_MODE2_MASK)
			| GPIO_P_MODEL_MODE2_INPUT;

	/* Pin PC3 is configured to Push-pull */
	GPIO->P[2].MODEL = (GPIO->P[2].MODEL & ~_GPIO_P_MODEL_MODE3_MASK)
			| GPIO_P_MODEL_MODE3_PUSHPULL;
	// [Port C Configuration]$
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
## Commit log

2016-12-27 sigilent sig gen examples
2016-12-27 neopixel generator
2017-05-05 add powermgr
2017-06-17 add LEDs and pulldowns
2017-06-18 almost done
2017-06-18 copper filling, thicker power tracks
2017-07-20 so-8 version, I bought wrong part number..
2017-07-22 fixups and text
2017-08-03 fixes
2017-09-24 reorganize
2017-09-24 usable code + some interrupt testing
2017-09-24 drop arduino stuff
2017-11-02 add fan pwm
2017-11-25 ugly cli prototype
2017-11-25 simple cli
2017-11-26 basic neopixel support
2017-12-03 test new GCC thingy
2017-12-03 support leds
2017-12-19 ad stuff
2018-07-22 ad2 worksheets
2018-09-22 init
2018-09-22 kicad stuff
2019-04-24 trying to make cmake work
2019-04-24 all the things
2019-04-24 compiles under clion
2019-04-28 make shit work
2019-04-28 prepare to add usb support
2019-04-28 playing around with graphics
2019-04-28 fix includes
2019-04-28 usb mode seems to work
2019-04-28 different timer per mode
2019-10-22 limesdr front plate
2019-11-05 add leds
2020-04-26 draft
2020-09-06 blinky on bluepill
2020-09-18 it bleeps
2020-09-20 beep boop
2020-09-20 test "song"
2020-09-20 trying to make 1MHz timer work
2020-09-20 generate MHz for real SID
2020-09-24 midi
2020-09-24 basic polyphony
2021-02-06 micro routed
2021-02-13 base layoyut done
2021-03-07 stuff

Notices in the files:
leaflet/source/InitDevice.c:
$[TIMER0 CC0 init]
$[TIMER1 CC0 init]
